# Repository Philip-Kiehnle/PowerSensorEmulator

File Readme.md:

# Motivation
To measure household electricity consumption in a typical photovoltaic or battery system in Germany, an additional power sensor is installed alongside the grid operator's electricity meter. This additional power sensor can be accessed directly by the Hybrid- or Batteryinverter, because a compatible model is installed by the PV installer or electrician.  
Many models use a Modbus RTU (RS-485) interface with a typical update rate of 1 to 4 Hz.

System overview:

This setup has some advantages and disadvantages.  
Disadvantages:
- Device cost of 100–300 € for the extra power sensor
- Installation cost, electrician needed
- Space required in the cabinet
- Power offset between grid operator's electricity meter and extra power sensor, 3–10 Watt
- Power consumption of the device, 0.4–2 Watt
- Minimal voltage/power loss in the main power cable, e.g. due to:
  - Longer cables have to be installed for the measurement setup.
  - A power sensor with an internal current measuring path is installed, as in the [Kaco Hy-switch](https://github.com/Philip-Kiehnle/kaco_blueplanet_hybrid10/tree/main/power_sensor).
  - Clamp current sensors have some loss in their cores.

Advantages:
+ Decent update rate of the power measurement enables fast settling time of the control loop
+ High reliability of the setup because of compatible power meter and inverter
 (Both arguments may be neglected in the future, see section [Impact on system performance](#impact-on-system-performance))

-> Let's take a different approach and use the "already there" optical infrared interface from the grid operator's energy/power meter and develop a protocol conversion adapter that behaves like a compatible power sensor.

# STM32 Microcontroller used as an Emulator for Chint Smart Power Sensor

The first prototype uses an optical read head, a microcontroller, and an RS-485 transceiver.

The optical read head is magnetically attached to the optical interface of the electricity meter. These readers are available online in several versions. Some include a WiFi module such as an ESP32, but for this project the bare UART output model is used. The read head converts the optical UART to an electrical UART signal. The UART signal is connected to the microcontroller, which decodes the Smart Message Language (SML) frames, sent by the electricity meter.  
Three elements are decoded:  

| OBIS code | Description                    | Variable name in software |
| --------- | ------------------------------ | ------------------------- |
| 16.7.0    | Sum active instantaneous power | power                     |
| 1.8.0     | Positive active energy total   | energy_import             |
| 2.8.0     | Negative active energy total   | energy_export             |

The STM32l432kc Nano devboard from ST Microelectronics was used. Its STM32L432KCU3 microcontroller runs at 32 MHz. The microcontroller implements a Modbus slave using the same registers as the original Chint power sensor. An RS-485 transceiver connects the microcontroller and the inverter (Huawei SUN2000-10KTL).

A breadboard was soldered to add connectors and the RS-485 transceiver.  
The prototype requires the following connections:
| Connector          | Description                                |
| ------------------ | ------------------------------------------ |
| USB-Power          | 5 V supply, e.g. from a 230 V power supply |
| Infrared Read Head | 4 pins for the infrared adapter: VCC, GND, TX, RX.<br>TX can be used in future software version to (re-)enter the meter key in case of a reset during a power outage. The manual [key input procedure](https://youtu.be/aqHauk3bNFA) can be avoided. |
| RS-485              | 2 pins for connection to the inverter     |

The prototype uses the following LED states:  
Yellow LED toggles with every decoded SML message of the Smart Meter.  
Green LED toggles on activity on the RS-485 bus.  
Both LEDs toggle fast at 10 Hz when an error handler is called. A microcontroller reboot is triggered automatically after 60 seconds. 

The setup looks like this:

## Power Consumption
The device is powered from the 230 V grid using an USB power supply.  
The power consumption was measured using the ELV Energy Master power meter:  
5 V 500 mA power supply: 0.4-0.5 W  
Reference test: 5 V 2 A Samsung power supply: 0.4 W

## Cost
STM devboard 18 €  
IR Smart Meter Reader (bitshake UART) 24 €  
RS-485 IC 1 €  
-> 43 €  
-> In a redesigned solution, everything should fit in the infrared reader magnet head.  

## ToDo
Every ~3 month, the prototype needs a power reset, because the Huawei monitoring  shows an error.  
-> Log the communication frames during this situation.

The use of a Huawei battery is untested. If the inverter control loop does not expect the increased delay time of the power measurement, instabilities may occur. In this case, a dead-time compensation (DTC) such as a Smith predictor must be implemented in the power sensor emulator software.

# Chint Smart Power Sensor DTSU666-H

To find the register list of the original Chint Power Sensor, this repo was helpful:
https://github.com/lmatula/ha_chint_pm

## Power Consumption
Single phase connected, all current sensors connected. The power consumption was measured using the ELV Energy Master power meter:  
Display Backlight ON : 0.6 W / 0.6 VA  
Display Backlight OFF: 0.45 W / 0.45 VA

According to datasheet:
Voltage: < 1 W (per phase)  
Current: < 1 VA (per phase) < 20 mA (per phase)

According to Huawei online manual:  
Power consumption of voltage: ≤ 1.5 W / 6 VA  
Power consumption of current: Ib < 10 A : ≤ 0.2 VA   Ib ≥ 10 A :≤ 0.4 VA

### Findings
Data update rate of the Chint Power Sensor?  
-> Registers change with a rate of about 13.6 Hz.

Modbus read interval of the Huawei inverter?  
-> According to Modbus log between 3 and 4 Hz.

Is an exact voltage measurement necessary for the inverter to detect the correct installation of the Chint Power Sensor?  
-> Don't think so, because the original Chint sensor will be detected even if only one phase is connected.

# Data Comparison

Python Modbus register read, with a single phase connected to Chint Power Sensor:

| Key        | Chint Power Sensor           | STM32 Power Sensor Emulator |
|------------|------------------------------|-----------------------------|
| addr       | 3                            | 3                           |
| baud       | 11                           | 11                          |
| clre       | 0                            | 0                           |
| day        | 0                            | 1                           |
| dmpt       | 0.0                          | 0.0                         |
| expep      | 0.0                          | 0.0                         |
| freq       | 50.0                         | 50.0                        |
| hour       | 0                            | 1                           |
| ia         | 0.003000000026077032         | 0.0                         |
| ib         | 0.008999999612569809         | 0.0                         |
| ic         | 0.00800000037997961          | 0.0                         |
| impep      | 0.0                          | 0.0                         |
| irat       | 1                            | 1                           |
| meter_type | 1                            | 1                           |
| minutes    | 17                           | 1                           |
| month      | 0                            | 4                           |
| net        | 0                            | 0                           |
| pa         | 0.10000000149011612          | 0.0                         |
| pb         | 0.0                          | 0.0                         |
| pc         | 0.0                          | 0.0                         |
| pfa        | 1.0                          | 1.0                         |
| pfb        | 1.0                          | 1.0                         |
| pfc        | 1.0                          | 1.0                         |
| pft        | 1.0                          | 1.0                         |
| protocol   | 3                            | 3                           |
| pt         | 0.10000000149011612          | 0.0                         |
| q1eq       | 0.0                          | 0.0                         |
| q2eq       | 0.0                          | 0.0                         |
| q3eq       | 0.0                          | 0.0                         |
| q4eq       | 0.0                          | 0.0                         |
| qa         | 0.10000000149011612          | 0.0                         |
| qb         | 0.0                          | 0.0                         |
| qc         | 0.0                          | 0.0                         |
| qt         | 0.10000000149011612          | 0.0                         |
| rev        | 109                          | 109                         |
| secound    | 32                           | 1                           |
| ua         | 226.39999389648438           | 230.0                       |
| uab        | 226.6999969482422            | 400.0                       |
| ub         | 0.699999988079071            | 230.0                       |
| ubc        | 0.699999988079071            | 400.0                       |
| uc         | 0.0                          | 230.0                       |
| uca        | 226.39999389648438           | 400.0                       |
| ucode      | 701                          | 701                         |
| urat       | 10                           | 10                          |
| year       | 0                            | 2024                        |

# Ideas

## Power Supply Solutions
The 230 V AC power supply is impractical if there is no socket nearby.

### Inverter USB Port
The Huawei SUN2000-12KTL-M5 has a USB voltage of 5.01V, but the USB port is typically used by the WLAN dongle.  
USB GND is connected to data connector GND (~0,8Ohm).

### Energy Harvester for RS-485 Bus
Use 1.8 V or 3.3 V microcontroller supply voltage. 1.8 V is too low for RS-485 within spec.  
STM32: 84uA/MHz in run mode. On average, 1 MHz should be sufficient:  
$` 84\,\mathrm{\mu A} \cdot 1.8\,\mathrm{V} = 151\,\mathrm{\mu W} `$

Use a push-pull microcontroller pin as a half bridge of a boost converter and boost the available voltage/power during TX of the Huawei inverter to 3.3 V bus.  
As a backup, use 2 x 1.5 V Alkaline batteries or a Li-Ion cell.  
Does Huawei inverter use a 120 Ohm termination resistor?  
In this case, the RS-485 transceiver IC will probably consume too much energy during the transmission of the data registers to the inverter.

Test of available RS-485 bus power of a Huawei SUN2000-12KTL-M5:

RS-485 pins have 2.554 V and 2.084 V to GND.

Connected 470 Ohm from RS-485 pin to GND:  
0.147V -> 0.31mA; 0.046mW  
0.12V -> 0.26mA; 0.03mW  
-> no harvesting seems possible if the transceiver is inactive.  
Or Impedance matching is necessary:  
(2.554V-0.147V)/0.31mA=7.76kOhm  
-> ((2.554V/2)^2)/(7.76k/2)=0.42mW

Energyharvesting during TX of the inverter:  
Duration of bus activity?

# Impact on System Performance
The grid operator's electricity meter may not send the current power via its optical interface per default. A pin code from the grid operator has to be entered via the optical interface with a torch, so the meter sends the actual power every second (1 Hz). The extra meter has a typical update rate of 1 to 4 Hz, but devices with higher update rates are available (e.g. [Kaco Hy-switch](https://github.com/Philip-Kiehnle/kaco_blueplanet_hybrid10/tree/main/power_sensor)).

The ISKRA MT175 and MT631 electricity meters store energy consumption in 0.1 Wh increments. This equals a consumption of 360 Watt for 1 second. A hint for this step size is the printed marking "10000 imp/kWh" on the meter housing.  
For larger load steps, the electricity meter counts the mismatch between battery inverter power and consumption.

Let's compare the system behavior using the grid operator's electricity meter as a power sensor versus a dedicated power sensor.  
Assumptions:
1. Dedicated power sensor and inverter control loop are super-fast and no mismatch due to load steps occurs.
2. Dedicated power sensor has a power consumption of 1 W.
3. Dedicated power sensor has 5 W offset.
4. Power loss in the current sensor cores is neglected.
5. Power sensor emulator has a power consumption of 0.4 W
6. During cooking with a glass ceramic hob at a medium power level, 2 kW load steps occur with a period of 5 sec on 5 sec off. This power level is used for 30 minutes every day. In 50% of the cooking sessions, the PV input is so high that there is no mismatch.
7. The inverter power matches the load 2 sec after the load step occurs.
8. Electricity price is 0.3 € per kWh.
9. Cost of feed-in from battery: 0.15 €. (When mismatch causes feed-in, battery power is fed to grid for feed-in tariff. But must be purchased again, when battery gets empty.)
10. Feed-in tariff: 0.08 €
11. In 50% of the 24/7 self-consumption, PV power feed-in is available.

**Dedicated Power Sensor**  
In one year, the dedicated power sensor self-consumption causes:  
$`8760\,\mathrm{h} \cdot (5\,\mathrm{W} + 1\,\mathrm{W}) = 52.6\,\mathrm{kWh}`$  
grid consumption and no extra feed-in from the battery.

**Power Sensor Emulator (Smart Meter Adapter)**  
In one year, the power sensor emulator causes:  
$`8760\,\mathrm{h} \cdot 0.4\,\mathrm{W} = 3.5\,\mathrm{kWh}`$  
grid consumption.  
Using the grid operator's electricity meter, the system causes mismatch only when the glass ceramic hob is used. The mismatch during a cooking session using the medium power level causes the grid consumption / feed-in scheme:
- **2 sec × 2 kW** grid **consumption**  
- **3 sec × 0 kW** grid **consumption**  
- **2 sec × 2 kW** grid **feed-in**  
- **3 sec × 0 kW** grid **feed-in**

This situation occurs for $`50\% \cdot 30\,\mathrm{min} = 0.25\,\mathrm{h}
`$  
So the energy impact is: $`
\left( \frac{2\,\mathrm{s}}{10\,\mathrm{s}} \cdot 0.25\,\mathrm{h} \right) \cdot 2\,\mathrm{kW} = 0.1\,\mathrm{kWh}`$
grid consumption and the same amount of grid feed-in.  
Annually, this sums up to:  
$`365 \cdot 0.1\,\mathrm{kWh} = 36.5\,\mathrm{kWh}`$

**Economical Perspective**  
<ins>Initial cost:</ins>  
Cost of extra power sensor: 100 € + 150 € installation  
Cost of power sensor emulator: 50 € + self-installation (no electrician needed)

<ins>Runtime cost in 15 years:</ins>  
Dedicated power sensor:  
$` 15\,\mathrm{years} \cdot 52.56\,\mathrm{kWh} \cdot (0.3\,\text{€/kWh} + 0.08\,\text{€/kWh})/2 = 149.8\,€`$  
Power sensor emulator:  
$` \begin{aligned} 15\,\mathrm{years} \cdot & ( 3.5\,\mathrm{kWh} \cdot (0.3\,\text{€/kWh} + 0.08\,\text{€/kWh})/2\\ & + 36.5\,\mathrm{kWh} \cdot (0.3\,\text{€/kWh} + 0.15\,\text{€/kWh})) = 256.35\,€ \end{aligned}`$

<ins>Overall Cost:</ins>  
Dedicated power sensor: 250 € + 149.8 € = **399.8 €**  
Emulator: 50 € + 256.35 € = **306.35 €**

**Outlook**
- A predictive controller can improve the mismatch, by learning the behavior of the glass ceramic hob and the user.
- A custom inverter with direct input of SML data without a protocol translator can improve the loop settling time to e.g. 1.1 sec instead of 2 sec. A GaN-based [PV battery inverter](https://github.com/Philip-Kiehnle/PVBatteryInverter) using this feature is under development.
- The grid operator's electricity meter should not count in tiny 0.1 Wh steps (increments). A step size to compensate a 3.6 kW load within 10 seconds should be suitable. This corresponds to 10 Wh increments.

# Background Story
The project was triggered by a friend with a Huawei SUN2000-10KTL inverter, who wanted to buy a Huawei Luna battery. After some research, I found that the Huawei battery is not a typical high voltage battery. It consists of stackable 48 V battery modules with an internal DCDC converter. However, the module voltage does not add up as usual because the modules are connected in parallel. The top stack contains another DCDC converter, and I had my doubts about its efficiency, especially at low loads, which occur overnight. [Application Note: Energy Efficiency of Smart String Energy Storage
System LUNA2000](https://www.photovoltaikforum.com/core/attachment/426947-application-note-luna2000-efficiency-pdf/)  
In order to check the household's electricity consumption at night, we wanted to log the data. The PV installer sold the power meter for the system some years ago, but did not install it. So the original Chint power sensor can be used for protocol reverse engineering and to develop the protocol adapter.

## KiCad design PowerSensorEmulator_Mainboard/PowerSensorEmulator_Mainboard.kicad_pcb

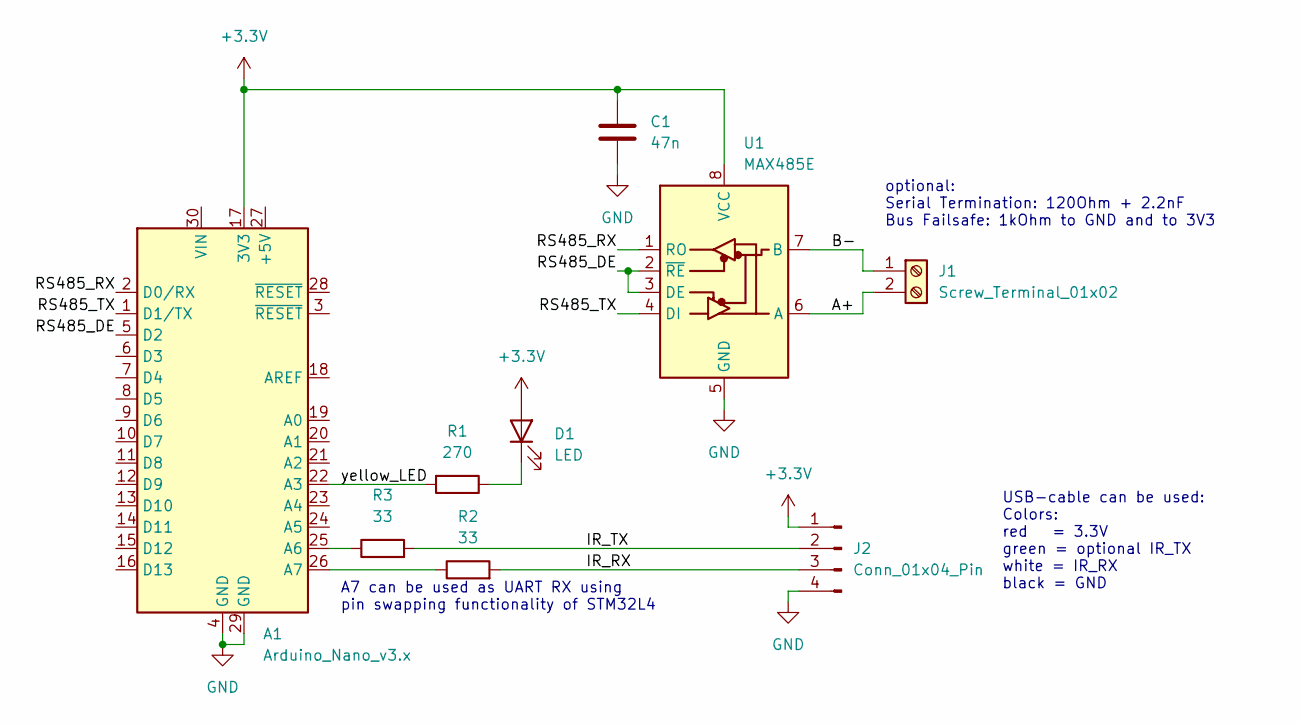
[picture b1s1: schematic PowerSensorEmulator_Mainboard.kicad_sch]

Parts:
A1: Arduino_Nano_v3.x; Arduino_Nano
C1: 47n; C_Disc_D3.0mm_W1.6mm_P2.50mm
D1: LED; LED_D2.0mm_W4.8mm_H2.5mm_FlatTop
J1: Screw_Terminal_01x02; TerminalBlock_Phoenix_MKDS-1,5-2-5.08_1x02_P5.08mm_Horizont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
J2: Conn_01x04_Pin; PinHeader_1x04_P2.54mm_Vertical
R1: 270; R_0805_2012Metric
R2, R3: 33; R_0805_2012Metric
U1: MAX485E; DIP-8_W7.62mm

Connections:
+3.3V: A1.17 (3V3), C1.1, D1.2 (A), J2.1, U1.8 (VCC)
/A+: J1.2, U1.6 (A)
/B-: J1.1, U1.7 (B)
/IR_RX: J2.3, R2.2
/IR_TX: J2.2, R3.2
/RS485_DE: A1.5 (D2), U1.2 (~RE), U1.3 (DE)
/RS485_RX: A1.2 (D0/RX), U1.1 (RO)
/RS485_TX: A1.1 (D1/TX), U1.4 (DI)
/yellow_LED: A1.22 (A3), R1.2
GND: A1.4 (GND), A1.29 (GND), C1.2, J2.4, U1.5 (GND)
unnamed: A1.25 (A6), R3.1
unnamed: A1.26 (A7), R2.1
unnamed: D1.1 (K), R1.1

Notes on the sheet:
USB-cable can be used: Colors: red = 3.3V green = optional IR_TX white = IR_RX black = GND
A7 can be used as UART RX using pin swapping functionality of STM32L4
optional: Serial Termination: 120Ohm + 2.2nF Bus Failsafe: 1kOhm to GND and to 3V3

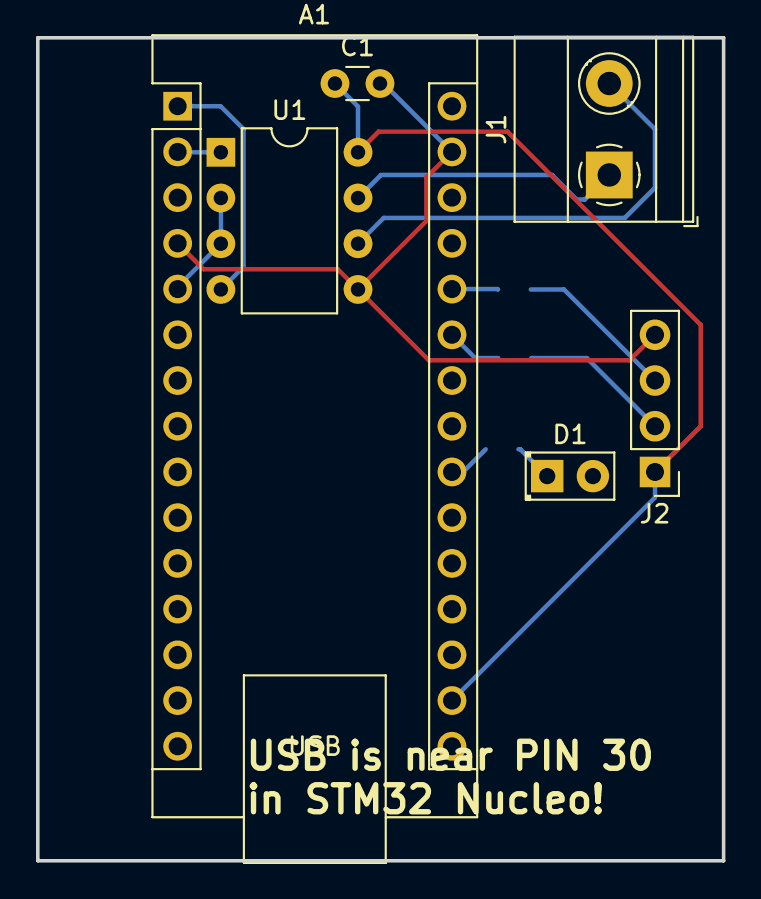
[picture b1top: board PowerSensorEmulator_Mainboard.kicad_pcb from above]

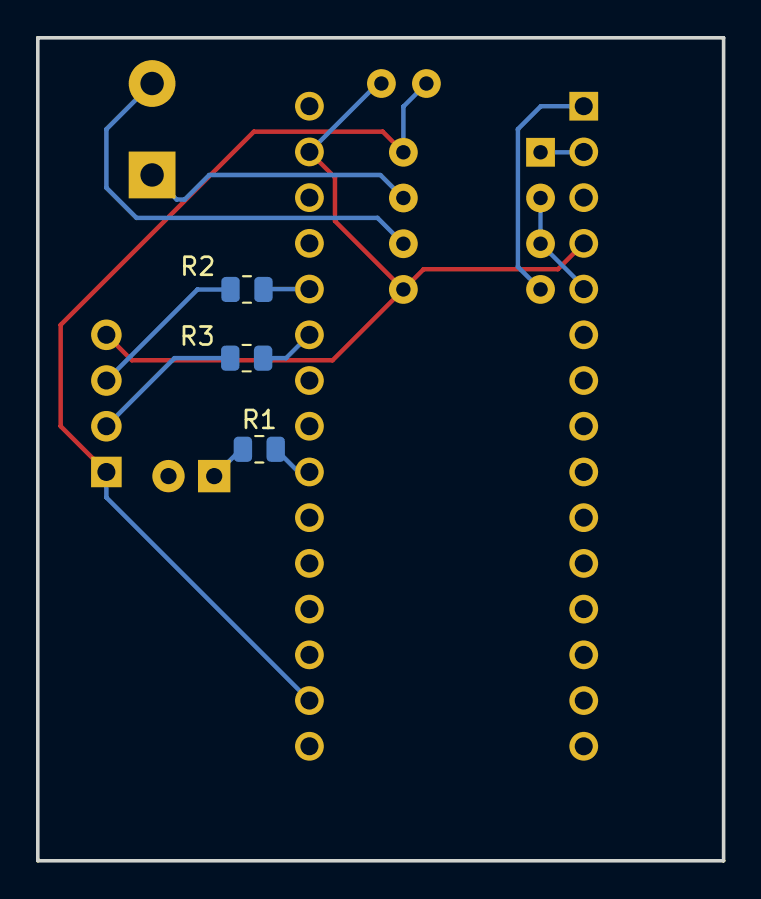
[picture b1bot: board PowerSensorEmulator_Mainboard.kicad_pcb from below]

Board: 2 copper layers, 38.1 x 45.7 mm, 9 parts (3 on the bottom side), 13 nets.

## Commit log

2025-05-06 RS485 and IR meter inferface work simultaneously; Huawei inverter shows household power in Fusion Solar app
